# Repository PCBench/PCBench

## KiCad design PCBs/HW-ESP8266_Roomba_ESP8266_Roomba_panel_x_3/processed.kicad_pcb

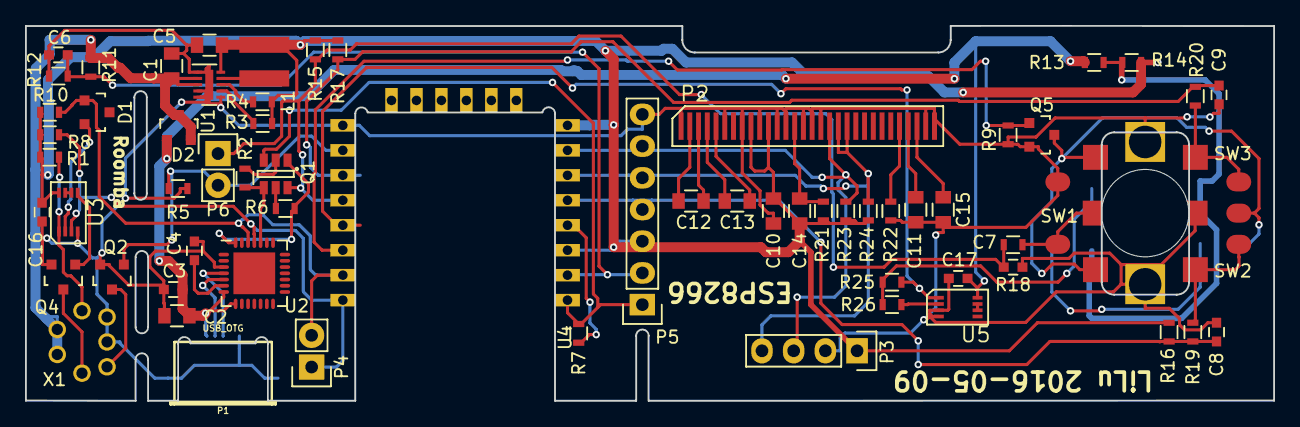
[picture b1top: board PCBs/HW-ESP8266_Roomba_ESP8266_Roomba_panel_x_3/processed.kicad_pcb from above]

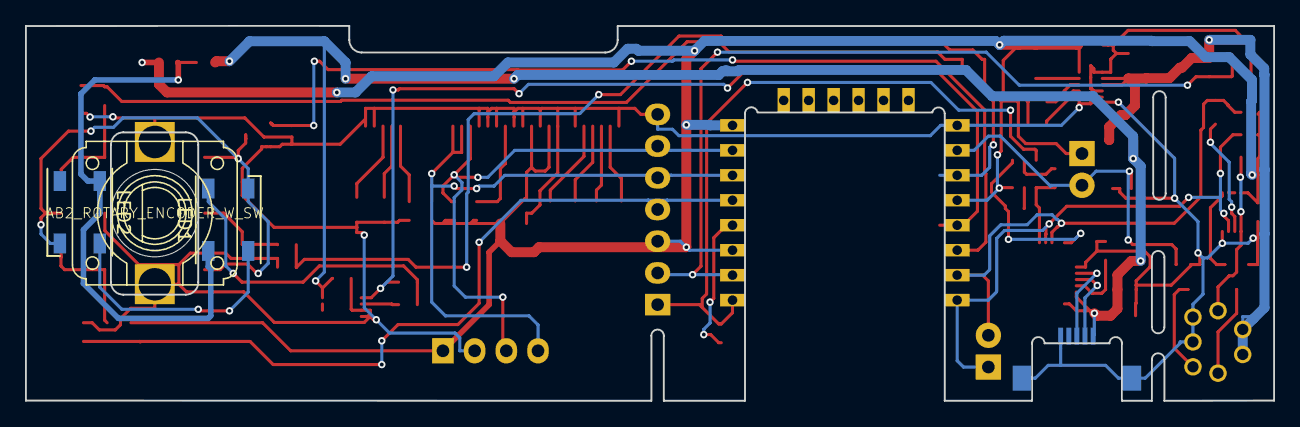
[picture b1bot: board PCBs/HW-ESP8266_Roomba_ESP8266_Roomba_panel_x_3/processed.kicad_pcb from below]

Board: 2 copper layers, 100.0 x 30.0 mm, 68 parts (3 on the bottom side), 50 nets.

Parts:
C1, C11, C14, C15: 2u2; C_0805
C2, C10, C12, C13: 1u; C_0805
C3, C4, C6, C7, C8, C9, C16, C17: 100n; C_0603
C5: 22u; C_0805
D1, D2: D_Schottky_x2_ACom_AKK; SOT-23
L1: VLS4012ET-100M
LED1, LED2: WS2812B; LED_WS2812B-PLCC4
P1: USB_OTG; conn_usb_B_micro_smd-backside
P2: UG_62864
P3: CONN_01X04; Pin_Header_Straight_1x04
P4, P6: CONN_01X02; Pin_Header_Straight_1x02
P5: CONN_01X07; Pin_Header_Straight_1x07
Q1: DMC204010R; SOT-23-6
Q2, Q4, Q5: 2N7002; SOT-23
R1: 1M; R_0603
R2, R6, R7, R15, R16, R17, R21, R23, R24: 10k; R_0603
R3, R4, R5, R8, R9, R10, R11, R12: 100k; R_0603
R13, R14, R25, R26: 0R; R_0603
R18, R19, R20: 1k; R_0603
R22: 390k; R_0603
ROT_ENC1: AB2_ROTARY_ENCODER_W_SW; ROT_ENC_backside
SW1, SW2, SW3: SW_PUSH; switch3x6_smd
U1: TPS62177; DFN-10-1EP_2x3mm_Pitch0.5mm
U2: CP2102; QFN-28-1EP_5x5mm_Pitch0.5mm
U3, U5: 74LVC3G14; VSSOP-8
U4: ESP-12E; ESP-12E_SideMounted
X1: MINI_DIN_7; MiniDin-7

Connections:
+3V3: C5.1, C10.1, C14.1, C16.1, L1.2, P2.9, P2.11, P3.1, P5.3, R1.2, R3.1, R4.1, R8.1, R10.1, R14.1, R15.2, R16.2, R17.2, R21.2, R23.2, R24.2, U1.10, U3.8, U4.8
+12V: C1.1, D2.2, D2.3, R11.1, U1.2, U1.3, X1.1, X1.2
/5V: C2.1, C3.1, C17.1, D2.1, P1.1, R13.2, U2.7, U2.8, U5.8
/ADC: C6.1, P5.2, R11.2, R12.1, U4.2
/DTR: Q1.1, R6.1, U2.28
/Enc_A: C9.1, R17.1, R20.2, U4.17
/Enc_B: C8.1, P5.4, R16.1, R19.2, U4.5
/LED: R25.2, U4.19, U5.1
/PowerOn: Q5.1, R9.2, U4.20
/RST: P5.1, Q1.3, R7.2, U4.1
/RTS: Q1.4, R2.1, U2.24
/RXD: D1.1, P4.2, R10.2, U2.26, U4.21
/Roomba_Wake: P6.2, Q2.1, R5.2, U4.16
/SCL: P2.18, P3.3, P5.6, R23.1, U4.7
/SDA: P2.19, P2.20, P3.4, P5.5, R24.1, U4.6
/Switch: C7.1, P6.1, Q1.6, R15.1, R18.2, U4.18
/TXD: P4.1, R8.2, U2.25, U3.3, U4.22
GND: C1.2, C2.2, C3.2, C4.2, C5.2, C6.2, C7.2, C8.2, C9.2, C11.2, C14.2, C15.2, C16.2, C17.2, P1.5, P1.6, P2.1, P2.6, P2.8, P2.10, P2.12, P2.13, P2.15, P2.16, P2.17, P2.29, P2.30, P3.2, P5.7, Q2.2, Q4.2, Q5.2, R5.1, R9.1, R12.2, R22.2, ROT_ENC1.6, ROT_ENC1.7, SW1.2, U1.1, U1.4, U1.5, U1.6, U1.11, U2.3, U3.4, U4.15, U5.3, U5.4, X1.6, X1.7
GNDPWR: LED1.3, LED2.3, Q5.3, ROT_ENC1.2, SW2.2, SW3.2
unnamed: C4.1, U2.6
unnamed: C10.2, P2.14, R21.1
unnamed: C11.1, P2.27
unnamed: C12.1, P2.2
unnamed: C12.2, P2.3
unnamed: C13.1, P2.4
unnamed: C13.2, P2.5
unnamed: C15.1, P2.28
unnamed: D1.2, U3.2
unnamed: L1.1, U1.9
unnamed: LED1.1, LED2.1, R13.1, R14.2
unnamed: LED1.2, LED2.4
unnamed: LED1.4, R25.1, R26.1
unnamed: P1.2, U2.5
unnamed: P1.3, U2.4
unnamed: P2.26, R22.1
unnamed: Q1.2, R2.2
unnamed: Q1.5, R6.2
unnamed: Q2.3, X1.5
unnamed: Q4.1, U3.5
unnamed: Q4.3, X1.3
unnamed: R1.1, U3.1, X1.4
unnamed: R3.2, U1.7
unnamed: R4.2, U1.8
unnamed: R7.1, U4.4
unnamed: R18.1, ROT_ENC1.4, SW1.1
unnamed: R19.1, ROT_ENC1.3, SW2.1
unnamed: R20.1, ROT_ENC1.1, SW3.1
unnamed: R26.2, U5.2
unnamed: U3.6, U3.7
unnamed: U5.6, U5.7

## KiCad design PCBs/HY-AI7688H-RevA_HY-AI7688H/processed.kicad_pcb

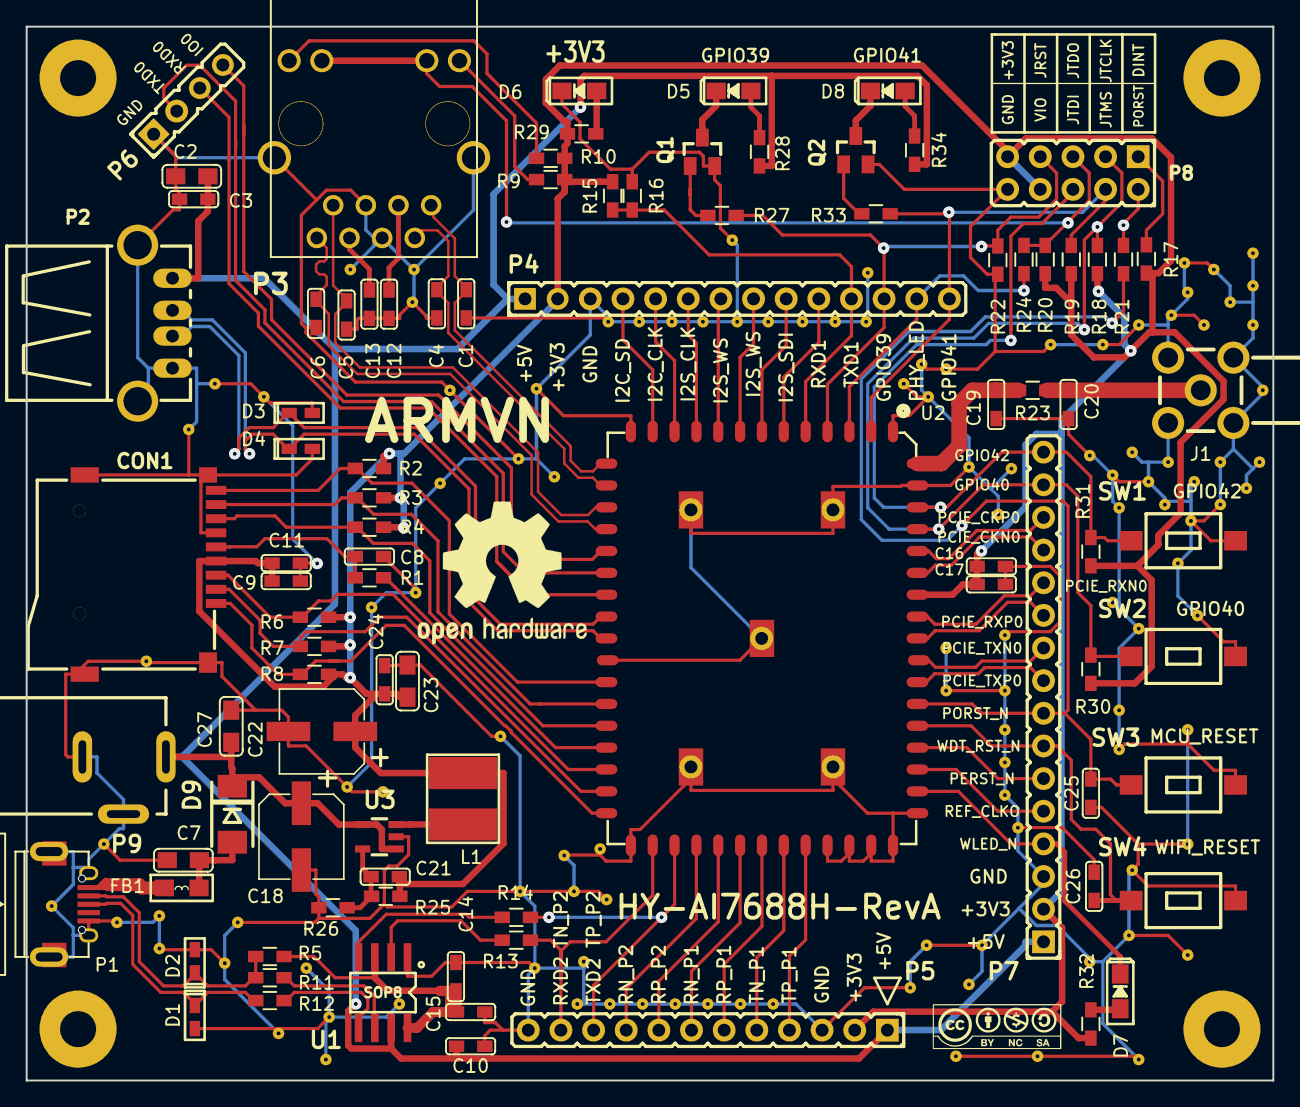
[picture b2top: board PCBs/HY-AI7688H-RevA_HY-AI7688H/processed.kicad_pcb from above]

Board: 2 copper layers, 97.0 x 82.0 mm, 96 parts (0 on the bottom side), 80 nets.

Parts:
C1, C4, C5, C6, C19, C20: DNP; CAPC0603x018M
C2, C7, C27: 10uF; CAPC0805X024M
C3, C10, C11, C12, C13, C14, C15, C17, C21, C24, C25, C26: 100nF; CAPC0603x018M
C8, C9: NC; CAPC0603x018M
C16: 100uF; CAPC0603x018M
C18, C22: 220uF/16V; CAPAE_6.3x7.7-M
C23: 22uF; CAPC0805X024M
CON1: TF-Micro-SDCard; TFC-WPAPR-08
D1, D2, D3, D4: TVS; DIOC_0603X018
D5, D6, D7, D8: LED; LED_0805x024M
D9: D_SS24; DO-214AA
FB1: FBM0805PT800S; FB0805x034M
J1: CONN_SMA; MOLEX_0731000114
L1: CDRH4D22; INDC5050X24M
MH1, MH2, MH3, MH4: MH_32.8MM; Mounting_hole_2.8mm
P1: USB_OTG; USB_Micro-B_DGK609-4048-1-ND
P2: USB_A; USB_A_H_PTH
P3: HR911102A
P4: CONN_01X14; HDRV14W64_1X14_3556X254X1154
P5: CONN_01X12; HDRV12W64_1X12_3048X254X1154
P6: CONN_01X04; HDRV4W64_1X4_1016X254X1154
P7: CONN_01X16; HDRV16W64_1X16_4046X254X1154
P8: CONN_02X05; HDRV10W64P254_2X5_1270X254X115P
P9: CONN-PWR-JACK; CONN_PWR_JACK_25
Q1, Q2: LMBT3904; SOT23-3-MMBT3904-M
R1, R13, R14, R21, R24: 22R; RESC0603x018M
R2, R3, R4, R6, R7, R8, R17, R30, R31: 10K; RESC0603x018M
R5: 1.5K; RESC0603x018M
R9, R10, R32: 330R; RESC0603x018M
R11, R12: 27R; RESC0603x018M
R15: 4.7K; RESC0603x018M
R16: DNP; RESC0603x018M
R18, R19, R20, R22: 1K; RESC0603x018M
R23: 0R; RESC0603x018M
R25: 47K_1%; RESC0603x018M
R26: 10.5K_1%; RESC0603x018M
R27, R33: 2.2K; RESC0603x018M
R28, R29, R34: 560R; RESC0603x018M
SW1: SW_USR1; SW-T1107A(6x3,8x2,5MM)
SW2: SW_USR2; SW-T1107A(6x3,8x2,5MM)
SW3: MPU_RESET; SW-T1107A(6x3,8x2,5MM)
SW4: WIFI_RESET; SW-T1107A(6x3,8x2,5MM)
U1: PL2303SA; SOP127P600x155-8-M
U2: AI7688H; AI7688H-M
U3: SY8008; SOT-23-5

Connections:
+3V3: C9.2, C11.2, C16.2, C17.2, C21.2, C22.1, C23.2, C24.2, CON1.4, L1.2, P4.2, P5.2, P7.2, P8.8, P8.9, R2.2, R3.2, R4.2, R6.2, R7.2, R8.2, R9.1, R10.1, R15.2, R17.2, R18.2, R19.2, R20.2, R25.2, R29.2, R30.2, R31.2, R32.1, U2.54
+5V: C2.2, C3.2, C10.2, C18.1, C27.2, D9.1, P2.1, P4.1, P5.1, P7.1, P9.1, R28.2, R34.2, U1.7, U3.1, U3.4
+5V_USBOTG: C7.2, D9.2, FB1.2
/AI7688H/D+: R12.1, U1.5
/AI7688H/D-: R11.1, U1.6
/AI7688H/EJTAG_DINT: P8.1, R17.1
/AI7688H/EJTAG_PORST_N: P8.2, R21.1
/AI7688H/EPHY_LED0_N: P3.10, P3.11, P8.5, R20.1, R24.2
/AI7688H/GPIO_0: P6.4, U2.18
/AI7688H/I2C_SCLK: P4.5, U2.11
/AI7688H/I2C_SD: P4.4, U2.12
/AI7688H/I2S_SCLK: P4.6, U2.10
/AI7688H/I2S_SDI: P4.9, U2.7
/AI7688H/I2S_SDO: P4.8, U2.8
/AI7688H/I2S_WS: P4.7, U2.9
/AI7688H/JRST_GPIO_39: P4.12, P8.7, R22.2, R27.1, U2.4
/AI7688H/JTCLK_GPIO_40: P7.15, P8.3, R18.1, R30.1, SW2.1, U2.57
/AI7688H/JTDI_GPIO_42: P7.16, P8.6, R31.1, SW1.1, U2.58
/AI7688H/JTDO_EPHY_LED0_N: P4.13, R24.1, U2.3
/AI7688H/JTMS_GPIO_41: P4.14, P8.4, R19.1, R33.1, U2.2
/AI7688H/MDI_P0_R_N: C4.2, P3.2, U2.15
/AI7688H/MDI_P0_R_P: C1.2, P3.1, U2.14
/AI7688H/MDI_P0_T_N: C6.2, P3.8, U2.17
/AI7688H/MDI_P0_T_P: C5.2, P3.7, U2.16
/AI7688H/MDI_RN_P1: P5.7, U2.36
/AI7688H/MDI_RN_P2: P5.9, U2.34
/AI7688H/MDI_RN_P3: CON1.7, R4.1, U2.26
/AI7688H/MDI_RN_P4: CON1.3, R6.1, U2.28
/AI7688H/MDI_RP_P1: P5.6, U2.37
/AI7688H/MDI_RP_P2: P5.8, U2.35
/AI7688H/MDI_RP_P3: CON1.8, R3.1, U2.25
/AI7688H/MDI_RP_P4: R1.1, U2.27
/AI7688H/MDI_TN_P1: P5.5, U2.38
/AI7688H/MDI_TN_P2: P5.11, R13.1, U2.32
/AI7688H/MDI_TN_P3: CON1.9, R2.1, U2.24
/AI7688H/MDI_TN_P4: CON1.1, R8.1, U2.30
/AI7688H/MDI_TP_P1: P5.4, U2.39
/AI7688H/MDI_TP_P2: P5.10, R14.1, U2.33
/AI7688H/MDI_TP_P4: CON1.2, R7.1, U2.29
/AI7688H/PCIE_CK0_N: P7.13, U2.55
/AI7688H/PCIE_CK0_P: P7.14, U2.56
/AI7688H/PCIE_RX0_N: P7.12, U2.53
/AI7688H/PCIE_RX0_P: P7.11, U2.52
/AI7688H/PCIE_TX0_N: P7.10, U2.51
/AI7688H/PCIE_TX0_P: P7.9, U2.50
/AI7688H/PERST_N: P7.6, U2.47
/AI7688H/PORST_N: C25.1, P7.8, R21.2, SW3.1, U2.49
/AI7688H/REF_CLKO: P7.5, U2.46
/AI7688H/RF: C19.2, R23.2, U2.60
/AI7688H/UART_7688_RXD0: P6.3, U2.20
/AI7688H/UART_7688_RXD1: P4.10, U2.6
/AI7688H/UART_7688_TXD0: P6.2, U2.19
/AI7688H/UART_7688_TXD1: P4.11, R15.1, R16.2, U2.5
/AI7688H/USB_D_N: D4.1, P2.2, U2.22
/AI7688H/USB_D_P: D3.1, P2.3, U2.21
/AI7688H/USB_OTG_D+: D1.1, P1.3, R12.2
/AI7688H/USB_OTG_D-: D2.1, P1.2, R5.1, R11.2
/AI7688H/WDT_RST_N: C26.1, P7.7, SW4.1, U2.48
/AI7688H/WLED_N: D7.1, P7.4, U2.45
GND: C1.1, C2.1, C3.1, C4.1, C5.1, C6.1, C7.1, C8.1, C9.1, C10.1, C11.1, C12.1, C13.1, C14.1, C15.1, C16.1, C17.1, C18.2, C19.1, C20.1, C22.2, C23.1, C24.1, C25.2, C26.2, C27.1, CON1.6, CON1.10, CON1.11, CON1.12, CON1.13, D1.2, D2.2, D3.2, D4.2, D6.1, J1.2, J1.3, J1.4, J1.5, P1.5, P1.6, P2.4, P2.5, P3.4, P3.5, P3.13, P3.14, P4.3, P5.3, P5.12, P6.1, P7.3, P8.10, P9.2, P9.3, Q1.2, Q2.2, R16.1, R22.1, R26.1, SW1.2, SW2.2, SW3.2, SW4.2, U1.1, U2.1, U2.13, U2.23, U2.31, U2.40, U2.41, U2.42, U2.43, U2.44, U2.59, U2.61, U2.62, U2.63, U2.64, U2.65, U3.2
unnamed: C8.2, CON1.5, R1.2
unnamed: C12.2, P3.3
unnamed: C13.2, P3.6
unnamed: C20.2, J1.1, R23.1
unnamed: C21.1, R25.1, R26.2, U3.5
unnamed: D5.1, Q1.3
unnamed: D5.2, R28.1
unnamed: D6.2, R29.1
unnamed: D7.2, R32.2
unnamed: D8.1, Q2.3
unnamed: D8.2, R34.1
unnamed: FB1.1, P1.1
unnamed: L1.1, U3.3
unnamed: P3.9, R9.2
unnamed: P3.12, R10.2
unnamed: Q1.1, R27.2
unnamed: Q2.1, R33.2
unnamed: R13.2, U1.2
unnamed: R14.2, U1.4
VO_3V3: C14.2, C15.2, R5.2, U1.3, U1.8

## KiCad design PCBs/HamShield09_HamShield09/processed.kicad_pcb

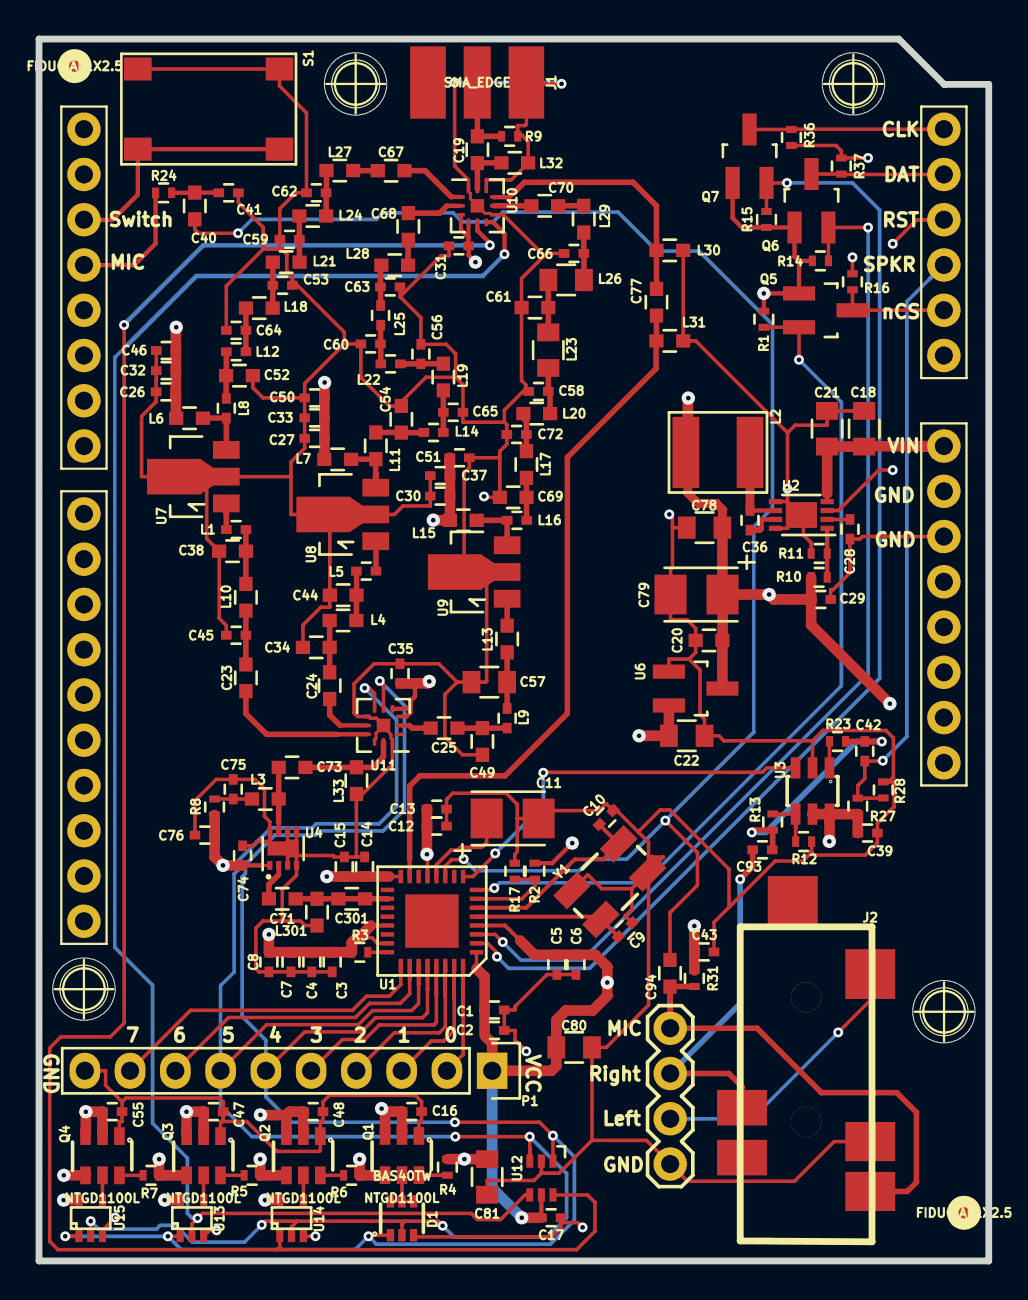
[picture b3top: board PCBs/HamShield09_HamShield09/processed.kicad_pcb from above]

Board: 4 copper layers, 53.3 x 68.6 mm, 173 parts (0 on the bottom side), 100 nets.

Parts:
C1, C3, C5, C7, C12, C14, C26, C27, C30, C41: 1n; C_0402
C2, C4, C6, C8, C16, C17, C31, C32, C33, C35, C36, C37, C39, C42, C43, C47, C48, C55, C74, C75, C76, C93: 0u1; C_0402
C9, C10, C15, C64: 10p; C_0402
C11, C79: 47u; C1210P
C13, C28, C29, C46, C50, C51: 1u; C_0402
C18, C21, C22, C78, C80: 10u; C_0805
C19, C23, C24, C25, C44, C67, C68, C70, C71, C73, C77: 100p; C_0603
C20: 4.7u; C_0603
C34, C52, C61: 24p; C_0603
C38: 56p; C_0603
C40, C94: 2u2; C_0603
C45, C60, C65: 15p; C_0402
C49, C54: 43p; C_0603
C53, C62: 7p; C_0402
C56, C63: 14p; C_0402
C57: 180p; C_0805
C58, C66: 20p; C_0402
C59: 8.2p; C_0402
C69: 68p; C_0603
C72: 27p; C_0402
C81: 22u; C_0805
C301: DNP; C_0603
D1: BAS40TW; SOT-363
FD1, FD2: FIDUCIAL1X2.5; SparkFun-FIDUCIAL-1X2.5
J1: SMA_EDGE; SMA-EDGE-HandSolder
J2: SJ-43514-SMT-TR
JP3: M04PTH; SparkFun-1X04
L1: 1ohm; C_0402
L2: NR5040T220M; NR5040
L3, L32, L33: 220n; C_0603
L4: 15n; C_0603
L5, L8: 3.6n; C_0402
L6, L7, L15: 100n; C_0603
L9: 24n; C_0402
L10, L13: 5.6n; C_0603
L11: 6.2n; C_0603
L12, L16: 12n; C_0402
L14: 18n; C_0402
L17, L21, L24: 33n; C_0603
L18, L27: 24n; C_0603
L19, L28: 47n; C_0603
L20, L29: 82n; C_0603
L22, L25: 75n; C_0402
L23, L26: 120n; C_0805
L30, L31, L301: DNP; C_0603
P1: CONN_01X10; Pin_Header_Straight_1x10
Q1, Q2, Q3, Q4: NTGD1100L; SC-74
Q5, Q6, Q7: BSS138; SOT-23_Handsoldering
R1, R4, R5, R6, R7, R9, R11, R14, R15, R16, R36, R37: 10k; R_0402
R2, R3, R13: 0; R_0402
R8: 1.8; R_0402
R10: 52.3k; R_0402
R12: dnp; R_0402
R17: DNP; R_0402
R23: 13.3; R_0402
R24: 20k; R_0402
R27, R28: 100k; R_0402
R31: 2k; R_0402
S1: TAC_SWITCHSMD; SWITCH_TACTILE_SMD_8mmX5mm
U1: AU1846; QFN32-5x5
U2: MCP16311; DFN-8-1EP_3x2mm_Pitch0.5mm
U3: AD8591; SOT23-6
U4: TRF37A75; DFN-8-1EP_2x2mm_Pitch0.5mm
U5: ARDUINO_SHIELD; ARDUINO_UNO_SHIELD
U6: AP2125N-3.3TRG1; SOT-23_Handsoldering
U7, U8, U9: TQP7M9105; SOT89-3_Housing
U10, U11: SKY13388; QFN-12-2mm-x-2mm
U12: NC7WZ14; SC-70-6
U13, U14, U15: NC7SZ08; sc70-5
Y1: 12.8MHz; SparkFun-CRYSTAL-SMD-5X3

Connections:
+5V: C20.1, C29.2, C31.1, C35.1, C78.2, C79.1, C81.2, L2.2, Q1.4, Q2.4, Q3.4, Q4.4, R4.1, R5.1, R6.1, R7.1, R10.1, U6.3, U10.3, U10.4, U11.3, U11.4
+5VL: R16.2, R36.2, R37.2, U5.5V
/GPIO0: P1.2, U1.32
/GPIO1: P1.3, U1.31
/GPIO2: P1.4, U1.30
/GPIO3: P1.5, U1.29
/GPIO6: P1.8, U1.26
/GPIO7: P1.9, U1.25
/Power Control/V1: D1.1, P1.6, U1.28, U11.5, U12.1, U13.1, U15.1
/Power Control/V2: D1.2, P1.7, U1.27, U11.6, U12.3, U14.2, U15.2
/Power Control/Y1: U10.5, U12.6, U14.1
/Power Control/Y2: U10.6, U12.4, U13.2
/Power Control/nRST: U2.3, U5.A3
/RF Front End/1.2m_IN: C24.1, U11.8
/RF Front End/1.2m_OUT: C68.1, U10.2
/RF Front End/2m_IN: C25.1, U11.2
/RF Front End/2m_OUT: C70.1, U10.8
/RF Front End/70cm_IN: C23.1, U11.9
/RF Front End/70cm_OUT: C67.1, U10.1
/RF Front End/ANT: C19.1, L32.2, U10.11
/RF Front End/RF_IN: C77.1, L31.1, U1.15
/RF Front End/RF_OUT: C71.2, C301.1, C301.2, L301.2, U1.18
/RF Front End/STAGE1_OUT: C73.1, L33.2, U11.11
/User Interface/AFOUT: U1.9, U3.3
/User Interface/ARD_AUDIO_OUT: C42.2, R27.1, R28.1, U5.A2
/User Interface/MIC_IN: C40.1, C94.1, U1.11
/User Interface/MODE: R2.1, R17.1, U1.7
/User Interface/PDN: R3.1, U1.24
/User Interface/PWM_AUDIO_IN: R24.2, U5.D3
/User Interface/SCLK: Q7.2, R15.1, U1.2
/User Interface/SDIO: Q6.2, R14.1, U1.3
/User Interface/nSEN: Q5.2, R1.1, U1.8
AVDD: C18.1, C21.1, U2.4, U5.VIN
GND: C1.2, C2.2, C3.2, C4.2, C5.2, C6.2, C7.2, C8.2, C9.2, C10.2, C11.2, C12.2, C13.2, C14.2, C15.2, C16.2, C17.1, C18.2, C20.2, C21.2, C22.1, C26.2, C27.2, C28.2, C29.1, C30.2, C31.2, C32.2, C33.2, C34.2, C35.2, C37.2, C38.2, C39.1, C41.1, C43.1, C44.2, C45.2, C46.2, C47.2, C48.2, C49.2, C50.2, C51.2, C52.2, C53.2, C54.2, C55.2, C56.2, C57.2, C58.2, C59.2, C60.2, C61.2, C62.2, C63.2, C64.2, C65.2, C66.2, C69.2, C72.2, C74.2, C75.2, C76.2, C78.1, C79.2, C80.1, C81.1, D1.3, J1.GND, J2.4, JP3.4, L30.2, L31.2, L32.1, L33.1, L301.1, P1.10, Q1.1, Q2.1, Q3.1, Q4.1, R9.2, R11.2, R12.1, R17.2, R28.2, S1.3, S1.4, U2.5, U2.8, U2.9, U3.2, U4.3, U4.4, U4.5, U4.6, U4.8, U4.9, U5.GP1, U5.GP2, U6.1, U7.2, U8.2, U9.2, U10.7, U10.10, U10.12, U10.13, U11.7, U11.10, U11.12, U11.13, U12.2, U13.3, U14.3, U15.3, Y1.2, Y1.4
unnamed: C9.1, U1.5, Y1.1
unnamed: C10.1, U1.6, Y1.3
unnamed: C11.1, U1.12
unnamed: C19.2, J1.SIG, R9.1
unnamed: C23.2, C45.1, L10.1
unnamed: C24.2, C34.1, L4.1
unnamed: C25.2, C49.1, L9.1
unnamed: C28.1, U2.2
unnamed: C36.1, U2.7
unnamed: C36.2, L2.1, U2.6
unnamed: C38.1, L1.1, L10.2
unnamed: C40.2, C41.2, R24.1
unnamed: C42.1, C93.1, R13.2, R23.2
unnamed: C44.1, L4.2, L5.1
unnamed: C52.1, L8.1, L12.2
unnamed: C53.1, L18.1, L21.2
unnamed: C54.1, L11.1, L14.2
unnamed: C56.1, L19.1, L22.2
unnamed: C57.1, L9.2, L13.1
unnamed: C58.1, L20.1, L23.2
unnamed: C59.1, L21.1, L24.2
unnamed: C60.1, L22.1, L25.2
unnamed: C61.1, L23.1, L26.2
unnamed: C62.1, L24.1, L27.2
unnamed: C63.1, L25.1, L28.2
unnamed: C64.1, L12.1, L18.2
unnamed: C65.1, L14.1, L19.2
unnamed: C66.1, L26.1, L29.2
unnamed: C67.2, L27.1
unnamed: C68.2, L28.1
unnamed: C69.1, L16.1, L17.2
unnamed: C70.2, L29.1
unnamed: C71.1, U4.2
unnamed: C72.1, L17.1, L20.2
unnamed: C73.2, L3.1, U4.7
unnamed: C75.1, L3.2, R8.1
unnamed: C77.2, L30.1, U10.9
unnamed: C93.2, J2.3, JP3.2
unnamed: C94.2, J2.1, JP3.1, R31.2
unnamed: D1.4, D1.5, D1.6, Q1.5
unnamed: J2.2, JP3.3
unnamed: L1.2, U7.1
unnamed: L5.2, U8.1
unnamed: L6.2, L8.2, U7.3
unnamed: L7.2, L11.2, U8.3
unnamed: L13.2, U9.1
unnamed: L15.2, L16.2, U9.3
unnamed: Q1.6, R4.2
unnamed: Q2.5, U14.4
unnamed: Q2.6, R6.2
unnamed: Q3.5, U13.4
unnamed: Q3.6, R5.2
unnamed: Q4.5, U15.4
unnamed: Q4.6, R7.2
unnamed: Q5.3, R16.1, U5.A1
unnamed: Q6.3, R37.1, U5.A4
unnamed: Q7.3, R36.1, U5.A5
unnamed: R10.2, R11.1, U2.1
unnamed: R12.2, R13.1, U3.4
unnamed: R23.1, U3.1
unnamed: S1.1, S1.2, U5.D2
VCC: C1.1, C2.1, C3.1, C4.1, C5.1, C6.1, C7.1, C8.1, C12.1, C13.1, C14.1, C15.1, C17.2, C22.2, C39.2, C80.2, P1.1, Q5.1, Q6.1, Q7.1, R1.2, R2.2, R3.2, R14.2, R15.2, R27.2, U1.1, U1.4, U1.13, U1.16, U1.21, U1.23, U3.5, U3.6, U6.2, U12.5, U13.5, U14.5, U15.5
VTX: C16.1, C43.2, C74.1, C76.1, Q1.2, Q1.3, R8.2, R31.1, U4.1
V_1.2M: C27.1, C33.1, C47.1, C50.1, L7.1, Q3.2, Q3.3
V_2M: C30.1, C37.1, C48.1, C51.1, L15.1, Q2.2, Q2.3
V_70CM: C26.1, C32.1, C46.1, C55.1, L6.1, Q4.2, Q4.3

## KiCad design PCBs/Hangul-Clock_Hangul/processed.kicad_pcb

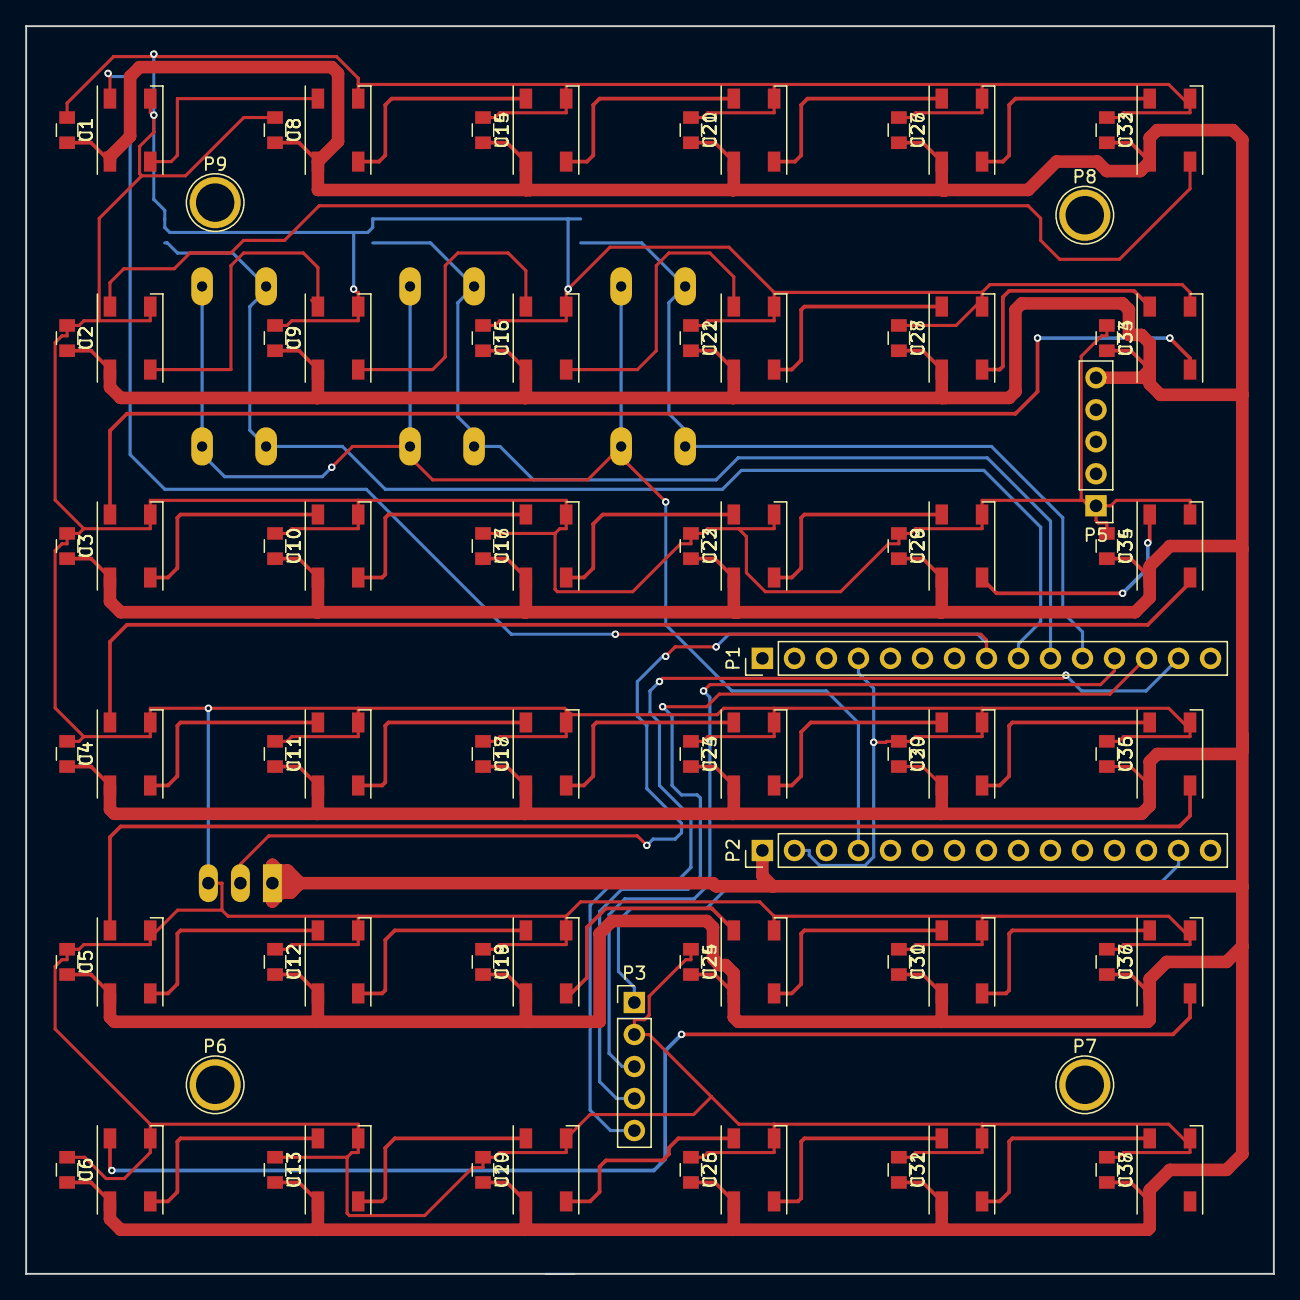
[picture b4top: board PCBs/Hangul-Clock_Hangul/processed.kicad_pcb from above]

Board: 2 copper layers, 99.0 x 99.0 mm, 87 parts (0 on the bottom side), 46 nets.

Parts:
C1, C2, C3, C4, C5, C6, C8, C9, C10, C11, C12, C13, C15, C16, C17, C18, C19, C20, C21, C22, C23, C24, C25, C26, C27, C28, C29, C30, C31, C32, C33, C34, C35, C36, C37, C38: C; C_0805
P1: NANO_1; Pin_Header_Straight_1x15_Pitch2.54mm
P2: NANO_2; Pin_Header_Straight_1x15_Pitch2.54mm
P3: DS1302; Pin_Header_Straight_1x05_Pitch2.54mm
P4: CONN_01X03; MOLEX-5045-03A
P5: POWER; Pin_Header_Straight_1x05_Pitch2.54mm
P6, P7, P8, P9: S; 1pin
R1, R2, R3: R; R_0805BCU
SW1: SW_R; SW_PUSH-12mmBCU
SW2: SW_G; SW_PUSH-12mmBCU
SW3: SW_B; SW_PUSH-12mmBCU
U1, U2, U3, U4, U5, U6, U8, U9, U10, U11, U12, U13, U14, U15, U16, U17, U18, U19, U20, U21, U22, U23, U24, U25, U26, U27, U28, U29, U30, U31, U32, U33, U34, U35, U36, U37: WS2812B; LED_WS2812B-PLCC4

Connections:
+5V: P2.4, SW1.1, SW2.1, SW3.1
+5VA: C1.2, C2.2, C3.2, C4.2, C5.2, C6.2, C8.2, C9.2, C10.2, C11.2, C12.2, C13.2, C15.2, C16.2, C17.2, C18.2, C19.2, C20.2, C21.2, C22.2, C23.2, C24.2, C25.2, C26.2, C27.2, C28.2, C29.2, C30.2, C31.2, C32.2, C33.2, C34.2, C35.2, C36.2, C37.2, C38.2, P2.1, P4.1, P5.5, U1.1, U2.1, U3.1, U4.1, U5.1, U6.1, U8.1, U9.1, U10.1, U11.1, U12.1, U13.1, U14.1, U15.1, U16.1, U17.1, U18.1, U19.1, U20.1, U21.1, U22.1, U23.1, U24.1, U25.1, U26.1, U27.1, U28.1, U29.1, U30.1, U31.1, U32.1, U33.1, U34.1, U35.1, U36.1, U37.1
CLK: P1.12, P3.3
DAT: P1.13, P3.4
DIN: P1.8, P4.2, U1.4
GND: C1.1, C2.1, C3.1, C4.1, C5.1, C6.1, C8.1, C9.1, C10.1, C11.1, C12.1, C13.1, C15.1, C16.1, C17.1, C18.1, C19.1, C20.1, C21.1, C22.1, C23.1, C24.1, C25.1, C26.1, C27.1, C28.1, C29.1, C30.1, C31.1, C32.1, C33.1, C34.1, C35.1, C36.1, C37.1, C38.1, P1.4, P2.2, P3.2, P4.3, P5.1, R1.1, R2.1, R3.1, U1.3, U2.3, U3.3, U4.3, U5.3, U6.3, U8.3, U9.3, U10.3, U11.3, U12.3, U13.3, U14.3, U15.3, U16.3, U17.3, U18.3, U19.3, U20.3, U21.3, U22.3, U23.3, U24.3, U25.3, U26.3, U27.3, U28.3, U29.3, U30.3, U31.3, U32.3, U33.3, U34.3, U35.3, U36.3, U37.3
unnamed: P1.9, R1.2, SW1.2
unnamed: P1.10, R2.2, SW2.2
unnamed: P1.11, R3.2, SW3.2
unnamed: P2.14, P3.1
unnamed: U1.2, U8.4
unnamed: U2.2, U9.4
unnamed: U2.4, U32.2
unnamed: U3.4, U33.2
unnamed: U10.2, U16.4
unnamed: U3.2, U10.4
unnamed: U11.2, U17.4
unnamed: U4.2, U11.4
unnamed: U12.2, U18.4
unnamed: U5.2, U12.4
unnamed: U13.2, U19.4
unnamed: U6.2, U13.4
unnamed: U14.2, U20.4
unnamed: U8.2, U14.4
unnamed: U15.2, U21.4
unnamed: U9.2, U15.4
unnamed: U16.2, U22.4
unnamed: U17.2, U23.4
unnamed: U18.2, U24.4
unnamed: U19.2, U25.4
unnamed: U20.2, U26.4
unnamed: U21.2, U27.4
unnamed: U22.2, U28.4
unnamed: U23.2, U29.4
unnamed: U24.2, U30.4
unnamed: U25.2, U31.4
unnamed: U26.2, U32.4
unnamed: U27.2, U33.4
unnamed: U28.2, U34.4
unnamed: U29.2, U35.4
unnamed: U30.2, U36.4
unnamed: U31.2, U37.4
unnamed: U4.4, U34.2
unnamed: U5.4, U35.2
unnamed: U6.4, U36.2
RST: P1.14, P3.5

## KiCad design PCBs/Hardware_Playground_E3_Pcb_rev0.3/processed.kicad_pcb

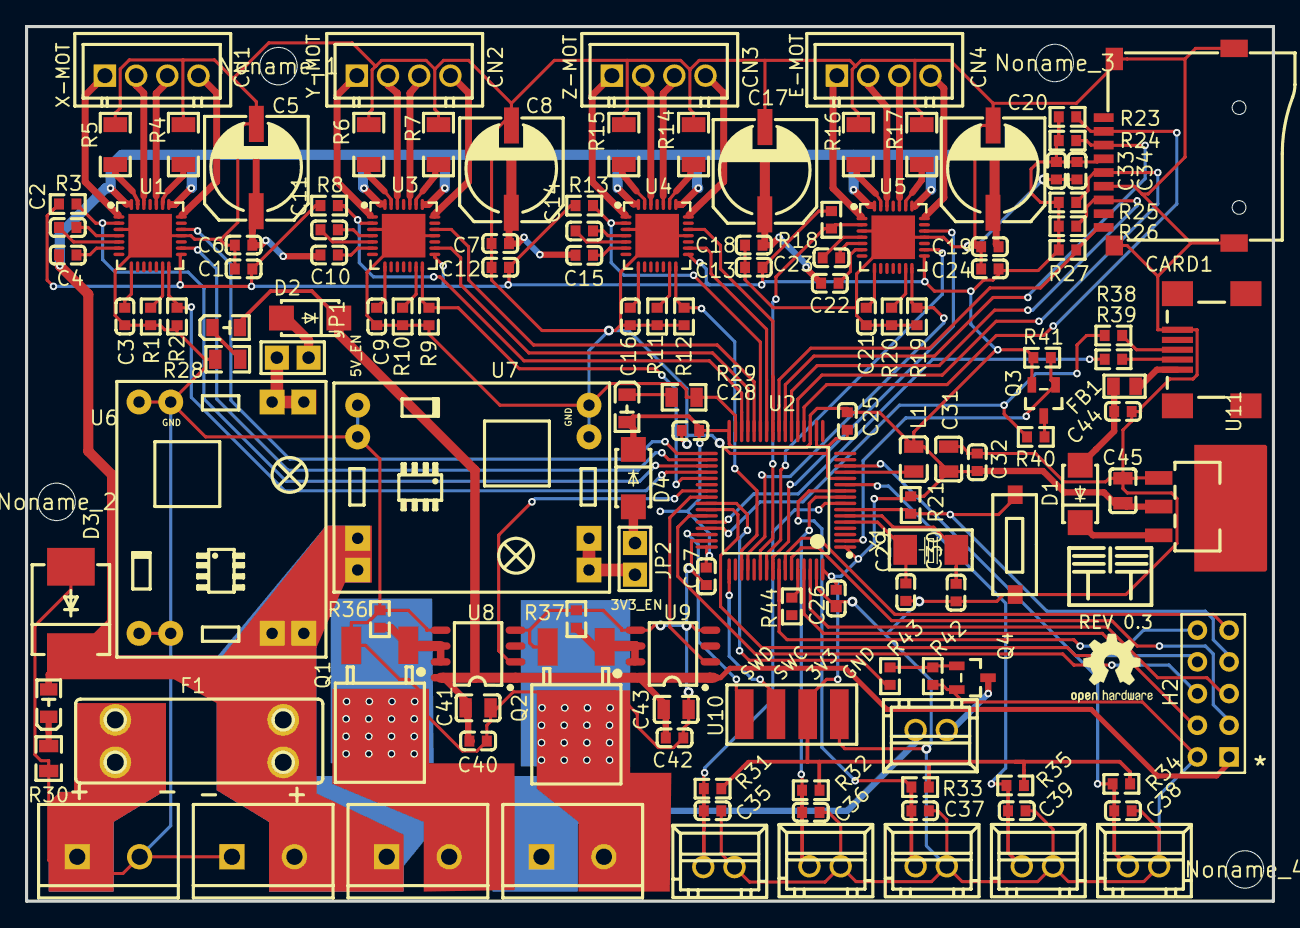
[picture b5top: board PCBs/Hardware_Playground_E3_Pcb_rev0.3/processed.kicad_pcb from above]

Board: 2 copper layers, 99.9 x 70.1 mm, 139 parts (0 on the bottom side), 114 nets.

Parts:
ALG: my_logo; ggeac4e8891367b2b2c
C1, C4, C6, C7, C10, C12, C13, C15, C18, C19, C22, C24, C25, C26, C27, C28, C32, C34, C35, C36, C37, C40, C42, C44: 100nF; C0603
C2, C11, C14, C23: 22nF; C0603
C3, C9, C16, C21, C33: 4.7uF; C0603
C5, C8, C17, C20: 100uF; CAP-SMD_BD8.0-L8.3-W8.3-FD
C29, C30: 36pF; C0603
C31, C41, C43: 10uF; CAP-SMD_BD8.0-L8.3-W8.3-FD
C38, C39: 10uF; C0603
C45: 22uF; CAP-SMD_BD8.0-L8.3-W8.3-FD
CARD1: microSD; TF-SMD_TF-15×15
CN1, CN2, CN3, CN4: XH-4AK M; CAP-SMD_BD8.0-L8.3-W8.3-FD
CN5: X-STOP; CAP-SMD_BD8.0-L8.3-W8.3-FD
CN6: Y-STOP; CAP-SMD_BD8.0-L8.3-W8.3-FD
CN7: Z-STOP; CAP-SMD_BD8.0-L8.3-W8.3-FD
CN8: B_TH; CAP-SMD_BD8.0-L8.3-W8.3-FD
CN9: E_TH; CAP-SMD_BD8.0-L8.3-W8.3-FD
CN10: E_FAN_PWM; CONN-TH_XH-2A
D1, D2, D4: SS34; CAP-SMD_BD8.0-L8.3-W8.3-FD
D3: SS36; SMC_L7.1-W6.2-LS8.1-RD
F1: 20A; KEYSTONE 3557-2
FB1: MH2029-300Y; L0805
H2: LCD; HDR-TH_10P-P2.54-V-R2-C5-S2.54
JP1: 1; JUMPER2
JP2: 2; JUMPER2
JP3: USB_MINI; USB-MINIB
KEY1: RST; KEY-3.0*6.0
L1: 22uH; L0805
LED2: 5V_PWR; CAP-SMD_BD8.0-L8.3-W8.3-FD
LED3: 3V3_PWR; CAP-SMD_BD8.0-L8.3-W8.3-FD
LED4: PWR_IN; CAP-SMD_BD8.0-L8.3-W8.3-FD
Noname_1, Noname_2, Noname_3, Noname_4: MountingHole_3.00mm
P1: PWR-IN; CAP-SMD_BD8.0-L8.3-W8.3-FD
P2: E_PWM; CAP-SMD_BD8.0-L8.3-W8.3-FD
P3: B_PWM; CAP-SMD_BD8.0-L8.3-W8.3-FD
P4: PWR-OUT; CAP-SMD_BD8.0-L8.3-W8.3-FD
Q1, Q2: IRLR8726TRPBF; CAP-SMD_BD8.0-L8.3-W8.3-FD
Q3: IRLML2244TRPBF; SOT-23-3_L2.9-W1.6-P1.90-LS2.8-BR
Q4: IRLML6346TRPBF; SOT-23-3_L2.9-W1.6-P1.90-LS2.8-BR
R1, R2, R3, R8, R9, R10, R11, R12, R13, R18, R19, R20: 20K; R0603
R4, R5, R6, R7, R14, R15, R16, R17: 0.18; CAP-SMD_BD8.0-L8.3-W8.3-FD
R21, R34, R35: 4.7K; R0603
R23, R24, R25, R26, R31, R32, R33, R44: 10K; R0603
R27: 1.8K; R0603
R28: 680; R0805
R29: 330; R0805
R30: 4.7K; R0805
R36, R37, R42: 100K; R0603
R38, R39: 27; R0603
R40, R41: 1.5K; R0603
R43: 10Ω; R0603
U1, U3, U4: TMC2208-LA-T; CAP-SMD_BD8.0-L8.3-W8.3-FD
U2: STM32F103RCT6; LQFP-64_L10.0-W10.0-P0.50-LS12.0-BL
U5: TMC2208-LA-T; QFN-28_L5.0-W5.0-P0.50-BL-EP
U6, U7: GND; MP1584 STEP DOWN MODULE - PCB
U8, U9: MCP1407-E/SN; CAP-SMD_BD8.0-L8.3-W8.3-FD
U10: ICSP; SMD PIN HEADER 1X4
U11: AMS1117-3.3; SOT-223-3_L6.5-W3.4-P2.30-LS7.0-BR
X1: 8MHz; OSC-SMD_L5.0-W3.2

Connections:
+3V3: C1.2, C12.2, C13.2, C24.2, C25.1, C26.1, C27.1, C28.1, C31.1, C32.2, C33.1, C34.1, C45.2, CARD1.4, D4.1, L1.1, LED3.2, Q3.2, R3.2, R8.2, R13.2, R18.2, R21.2, R23.2, R24.2, R25.2, R26.2, R27.2, R31.1, R32.1, R33.1, R34.2, R35.2, R41.2, U1.15, U2.1, U2.19, U2.32, U2.48, U2.64, U3.15, U4.15, U5.15, U10.2, U11.2
+5V: C40.1, C41.1, C42.1, C43.1, D2.1, H2.1, LED2.2, U8.1, U8.8, U9.1, U9.8
+VB: C4.2, C5.1, C6.2, C7.2, C8.1, C10.2, C15.2, C17.1, C18.2, C19.2, C20.1, C22.2, CN10.2, D3.2, F1.2, LED4.2, P2.1, P3.1, P4.2, U1.22, U1.28, U3.22, U3.28, U4.22, U4.28, U5.22, U5.28, U6.2, U7.2
BED_PWM: U2.40, U9.2
C9_1: C9.1, U3.8
C10_1: C10.1, U3.6
C11_1: C11.1, U3.4
C11_2: C11.2, U3.5
C21_1: C21.1, U5.8
C22_1: C22.1, U5.6
C23_1: C23.1, U5.4
C23_2: C23.2, U5.5
C44_1: C44.1, D1.2, FB1.2
E0_DIR: U2.56, U5.19
E0_EN: R18.1, U2.54, U5.2
E0_OA1: CN4.3, U5.24
E0_OA2: CN4.4, U5.21
E0_OB1: CN4.2, U5.26
E0_OB2: CN4.1, U5.1
E0_STP: U2.55, U5.16
E0_UART: R19.2, U2.52, U5.14
F1_1: F1.1, P1.1
FAN_PWM: R43.1, U2.41
FB1_1: FB1.1, JP3.VBUS
GND: C1.1, C3.2, C5.2, C6.1, C7.1, C8.2, C9.2, C12.1, C13.1, C16.2, C17.2, C18.1, C19.1, C20.2, C21.2, C24.1, C25.2, C26.2, C27.2, C28.2, C29.1, C30.1, C31.2, C32.1, C33.2, C34.2, C35.2, C36.2, C37.2, C38.2, C39.2, C40.2, C41.2, C42.2, C43.2, C44.2, C45.1, CARD1.6, CARD1.10, CARD1.11, CARD1.12, CARD1.13, CN5.2, CN6.2, CN7.2, CN8.2, CN9.2, D3.1, H2.2, JP3.GND, KEY1.2, P1.2, P4.1, Q1.3, Q2.3, Q4.2, R1.2, R2.1, R4.2, R5.2, R6.2, R7.2, R9.1, R10.2, R11.2, R12.1, R14.2, R15.2, R16.2, R17.2, R19.1, R20.2, R28.1, R29.1, R30.2, R36.1, R37.1, R42.1, U1.3, U1.18, U1.29, U2.12, U2.18, U2.31, U2.47, U2.63, U3.3, U3.18, U3.29, U4.3, U4.18, U4.29, U5.3, U5.18, U5.29, U6.1, U6.4, U7.1, U7.4, U8.4, U8.5, U9.4, U9.5, U10.1, U11.1
HE0_PWM: U2.39, U8.2
JP1_2: D2.2, JP1.2
JP2_2: D4.2, JP2.2
LCD_BEEP: H2.10, U2.57
LCD_CS: H2.4, U2.61
LCD_ENC_A: H2.6, U2.43
LCD_ENC_B: H2.8, U2.42
LCD_ENC_BTN: H2.9, U2.58
LCD_MOSI: H2.3, U2.59
LCD_SCK: H2.5, U2.62
Q1_2: P2.2, Q1.2
Q2_2: P3.2, Q2.2
Q3_3: Q3.3, R40.1
Q4_1: Q4.1, R42.2, R43.2
Q4_3: CN10.1, Q4.3
R10_1: R10.1, U3.13
R20_1: R20.1, U5.13
R28_2: LED2.1, R28.2
R29_2: LED3.1, R29.2
R30_1: LED4.1, R30.1
R37_2: Q2.1, R37.2, U9.6, U9.7
R38_1: JP3.D+, R38.1
R39_1: JP3.D-, R39.1
RESET: H2.7, KEY1.1, R21.1, U2.7
SD_CS: CARD1.2, R23.1, U2.20
SD_DET: CARD1.9, R27.1, U2.24
SD_MISO: CARD1.7, R26.1, U2.22
SD_MOSI: CARD1.3, R24.1, U2.23
SD_SCK: CARD1.5, R25.1, U2.21
SWCLK: U2.49, U10.3
SWDIO: U2.46, U10.4
TH0: C38.1, CN9.1, R34.1, U2.14
THB: C39.1, CN8.1, R35.1, U2.11
U1_4: C2.1, U1.4
U1_5: C2.2, U1.5
U1_6: C4.1, U1.6
U1_8: C3.1, U1.8
U1_13: R1.1, U1.13
U1_23: R4.1, U1.23
U1_27: R5.1, U1.27
U2_5: C29.2, U2.5, X1.1
U2_6: C30.2, U2.6, X1.2
U2_13: L1.2, U2.13
U2_60: R44.1, U2.60
U3_23: R7.1, U3.23
U3_27: R6.1, U3.27
U4_4: C14.1, U4.4
U4_5: C14.2, U4.5
U4_6: C15.1, U4.6
U4_8: C16.1, U4.8
U4_13: R11.1, U4.13
U4_23: R14.1, U4.23
U4_27: R15.1, U4.27
U5_23: R17.1, U5.23
U5_27: R16.1, U5.27
U6_3: JP1.1, U6.3
U7_3: JP2.1, U7.3
U8_6: Q1.1, R36.2, U8.6, U8.7
USB_CONN: Q3.1, R41.1, U2.2
USB_D+: R38.2, R40.2, U2.45
USB_D-: R39.2, U2.44
VUSB: D1.1, U11.3
X_DIR: U1.19, U2.33
X_EN: R3.1, U1.2, U2.35
X_OA1: CN1.3, U1.24
X_OA2: CN1.4, U1.21
X_OB1: CN1.2, U1.26
X_OB2: CN1.1, U1.1
X_STOP: C35.1, CN5.1, R31.2, U2.8
X_STP: U1.16, U2.34
X_UART: R2.2, U1.14, U2.36
Y_DIR: U2.28, U3.19
Y_EN: R8.1, U2.30, U3.2
Y_OA1: CN2.3, U3.24
Y_OA2: CN2.4, U3.21
Y_OB1: CN2.2, U3.26
Y_OB2: CN2.1, U3.1
Y_STOP: C36.1, CN6.1, R32.2, U2.9
Y_STP: U2.29, U3.16
Y_UART: R9.2, U2.37, U3.14
Z_DIR: U2.25, U4.19
Z_EN: R13.1, U2.27, U4.2
Z_OA1: CN3.3, U4.24
Z_OA2: CN3.4, U4.21
Z_OB1: CN3.2, U4.26
Z_OB2: CN3.1, U4.1
Z_STOP: C37.1, CN7.1, R33.2, U2.10
Z_STP: U2.26, U4.16
Z_UART: R12.2, U2.51, U4.14
